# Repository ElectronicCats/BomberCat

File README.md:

# BomberCat

<p align=center>

</p>

<p align=center><b>Where to buy and learn more</b></p>
<p align=center>

</p>

<p align=center>
  
</p>

BomberCat 💣 is the latest security tool that combines the most common card technologies: NFC technology (Near Field Communication) and magnetic stripe technology used in access control, identification, and banking cards.
Specially created to audit banking terminals, and identify NFC readers and sniffing tools, with this tool you can audit, read, or emulate magnetic stripes and NFC cards.

It also has an ESP32 co-processor with WiFiNINA firmware that allows it to make WiFi connections to use with HTTP or MQTT protocols, which will allow relay and spoofing attacks to be tested over long distances or on local web servers.

### Applications
BomberCat features an RP2040 MCU working along with the PN7150 (a recent generation NFC chip). 
The USB interface is provided by the RP2040 MCU and the NFC functionality is guaranteed by the PN7150.

BomberCat is designed to be intuitive for users. Easy to program using frameworks such as Arduino, Circuitpython, and Micropython.  We have prepared a series of examples with which you can start experimenting, check out the examples folder.

**Card emulation mode:** in which BomberCat behaves as a smart card or a tag. In this mode, BomberCat emulates an NFC tag. It does not initiate communication, it only responds to the NFC reader. 
A typical application of the card emulation mode is how people use NFC on their smartphones to replace several cards, badges, or tags at once (using the same smartphone for RFID access controls, contactless payments, etc). 
However, card emulation mode is not only beneficial for smartphones but any type of portable device.

**Read/Write:** in which BomberCat behaves as an NFC reader/writer. In this mode, BomberCat communicates with a passive tag, an NFC smart card, or an NFC device operating in the card emulation mode. It can read or write to a tag (although reading is a more common use case because tags will often be write-protected). In this mode, BomberCat generates an RF field, while a tag or card only modulates it.

**Magspoof:** for magnetic stripes interaction.
Magspoof mode can emulate magnetic stripe cards by emulating the electromagnetic pulses of this type of card.

## NFCGate relay

BomberCat can act as an [NFCGate](https://github.com/nfcgate/nfcgate)-compatible
**relay** endpoint: it pairs with a second NFCGate peer — another BomberCat or the
NFCGate Android app — through an `nfcgate-server`, relaying NFC APDUs over WiFi/TCP.
This makes a card that is physically in one place appear in front of a reader in
another — the classic test for whether a contactless reader accepts a card that is
not really present.

It ships with two pieces, each in its own repository:

- **Relay firmware** — [`bombercat-firmware`](https://github.com/ElectronicCats/bombercat-firmware),
  a role-selectable (`reader` / `card`) sketch built on the `BomberCatCore` library.
- **`bombercat` control CLI** — [`bombercat-tools`](https://github.com/ElectronicCats/bombercat-tools),
  a Python tool that configures, runs, monitors and captures the relay over
  USB-serial (APDU capture opens straight in Wireshark).

> Relay/spoofing features are for **authorized security audits only** — see the
> Disclaimer below.

## Characteristics:
- Cortex M0+ processor
- USB C 2.0
- NFC Reader, Card, and NFC Forum
- Arduino compatible
- 100% CircuitPython compatible
- UF2 Bootloader
- WIFI (WiFiNINA)
- BLE (ArduinoBLE)
- 1 LED status
- Open Hardware
- MagSpoof coil
- Battery
- RF protocols supported
  - NFCIP-1, NFCIP-2 protocol 
  - ISO/IEC 14443A, ISO/IEC 14443B PICC, NFC Forum T4T modes via host interface
  - NFC Forum T3T via host interface
  - ISO/IEC 14443A, ISO/IEC 14443B PCD designed according to NFC Forum digital protocol T4T platform and ISO-DEP 
  - FeliCa PCD mode
  - MIFARE Classic PCD encryption mechanism (MIFARE Classic 1K/4K)
  - NFC Forum tag 1 to 5 (MIFARE Ultralight, Jewel, Open FeliCa tag, MIFAREDESFire
  - ISO/IEC 15693/ICODE VCD mode 
  - Includes NXP ISO/IEC14443-A and Innovatron ISO/IEC14443-B intellectual property licensing rights

## Requirements

- **Arduino IDE:** version 2.3.3
- **Board Package:** Electronic Cats Mbed OS RP2040 Boards version 2.0.0

 Libraries:
 
  - **PubSubClient:** version 2.8.0
  - **WiFiNINA:** version 1.8.14
  - **Electronic Cats PN7150:** version 2.1.0
  - **SerialCommand:** [Arduino-SerialCommand](https://github.com/kroimon/Arduino-SerialCommand) 

### **Linux Setup Instructions**
If you are using Linux, ensure the BomberCat is properly recognized by running the post-install script located at:

`~/.arduino15/packages/electroniccats/hardware/mbed_rp2040/2.0.0/post_install.sh`

This step is essential to ensure the board can be detected and the firmware uploaded successfully.

## Wiki and Getting Started

[Getting Started in our Wiki](https://github.com/ElectronicCats/BomberCat/wiki)

## Repositories

This repository holds the **hardware** design (KiCad, BOM, mechanical files) and
general project documentation. Firmware and host tooling used to live here but were
split out into their own repositories for better version control and issue tracking:

### Firmware Repository
All BomberCat firmware (NFCGate relay, DetectTags, DetectReaders, magspoof, and more)
lives here:

https://github.com/ElectronicCats/bombercat-firmware

All BomberCat versions are supported in this repository — check which version you own
and select the proper branch to develop, build, or program your board.

### Tools Repository
The `bombercat` control CLI and other Python dev tooling live here:

https://github.com/ElectronicCats/bombercat-tools

## Disclaimer
>[!IMPORTANT]
>BomberCat is a wireless penetration testing tool intended **solely for use in authorized security audits, where such usage is permitted by applicable laws and regulations**. Before utilizing this tool, it is crucial to ensure compliance with all relevant legal requirements and obtain appropriate permissions from the relevant authorities.
>
>The board **does not provide** any means or authorization to utilize credit cards or engage in any financial transactions that are not legally authorized. **Electronic Cats holds no responsibility for any unauthorized use of the tool or any resulting damages**.

-------

## How to contribute 
 Contributions are welcome! 

Please read the document  [**Contribution Manual**](https://github.com/ElectronicCats/electroniccats-cla/blob/main/electroniccats-contribution-manual.md)  which will show you how to contribute your changes to the project.

✨ Thanks to all our [contributors](https://github.com/ElectronicCats/BomberCat/graphs/contributors)! ✨

See [**_Electronic Cats CLA_**](https://github.com/ElectronicCats/electroniccats-cla/blob/main/electroniccats-cla.md) for more information.

See the  [**community code of conduct**](https://github.com/ElectronicCats/electroniccats-cla/blob/main/electroniccats-community-code-of-conduct.md) for a vision of the community we want to build and what we expect from it.
 
### Supported by
 Thanks [Wallee](https://en.wallee.com/) for support this open source project

## Maintainer

<p align=center>

</p>

Electronic Cats invests time and resources providing this open-source design, please support Electronic Cats and open-source hardware by purchasing products from Electronic Cats!

### License

Electronic Cats invests time and resources in providing this open-source design, please support Electronic Cats and open-source hardware by purchasing products from Electronic Cats!

Designed by Electronic Cats.

Firmware released under an GNU AGPL v3.0 license. See the LICENSE file for more information.

Hardware released under an CERN Open Hardware Licence v1.2. See the LICENSE_HARDWARE file for more information.

Electronic Cats is a registered trademark, please do not use if you sell these PCBs.

Jul 2022

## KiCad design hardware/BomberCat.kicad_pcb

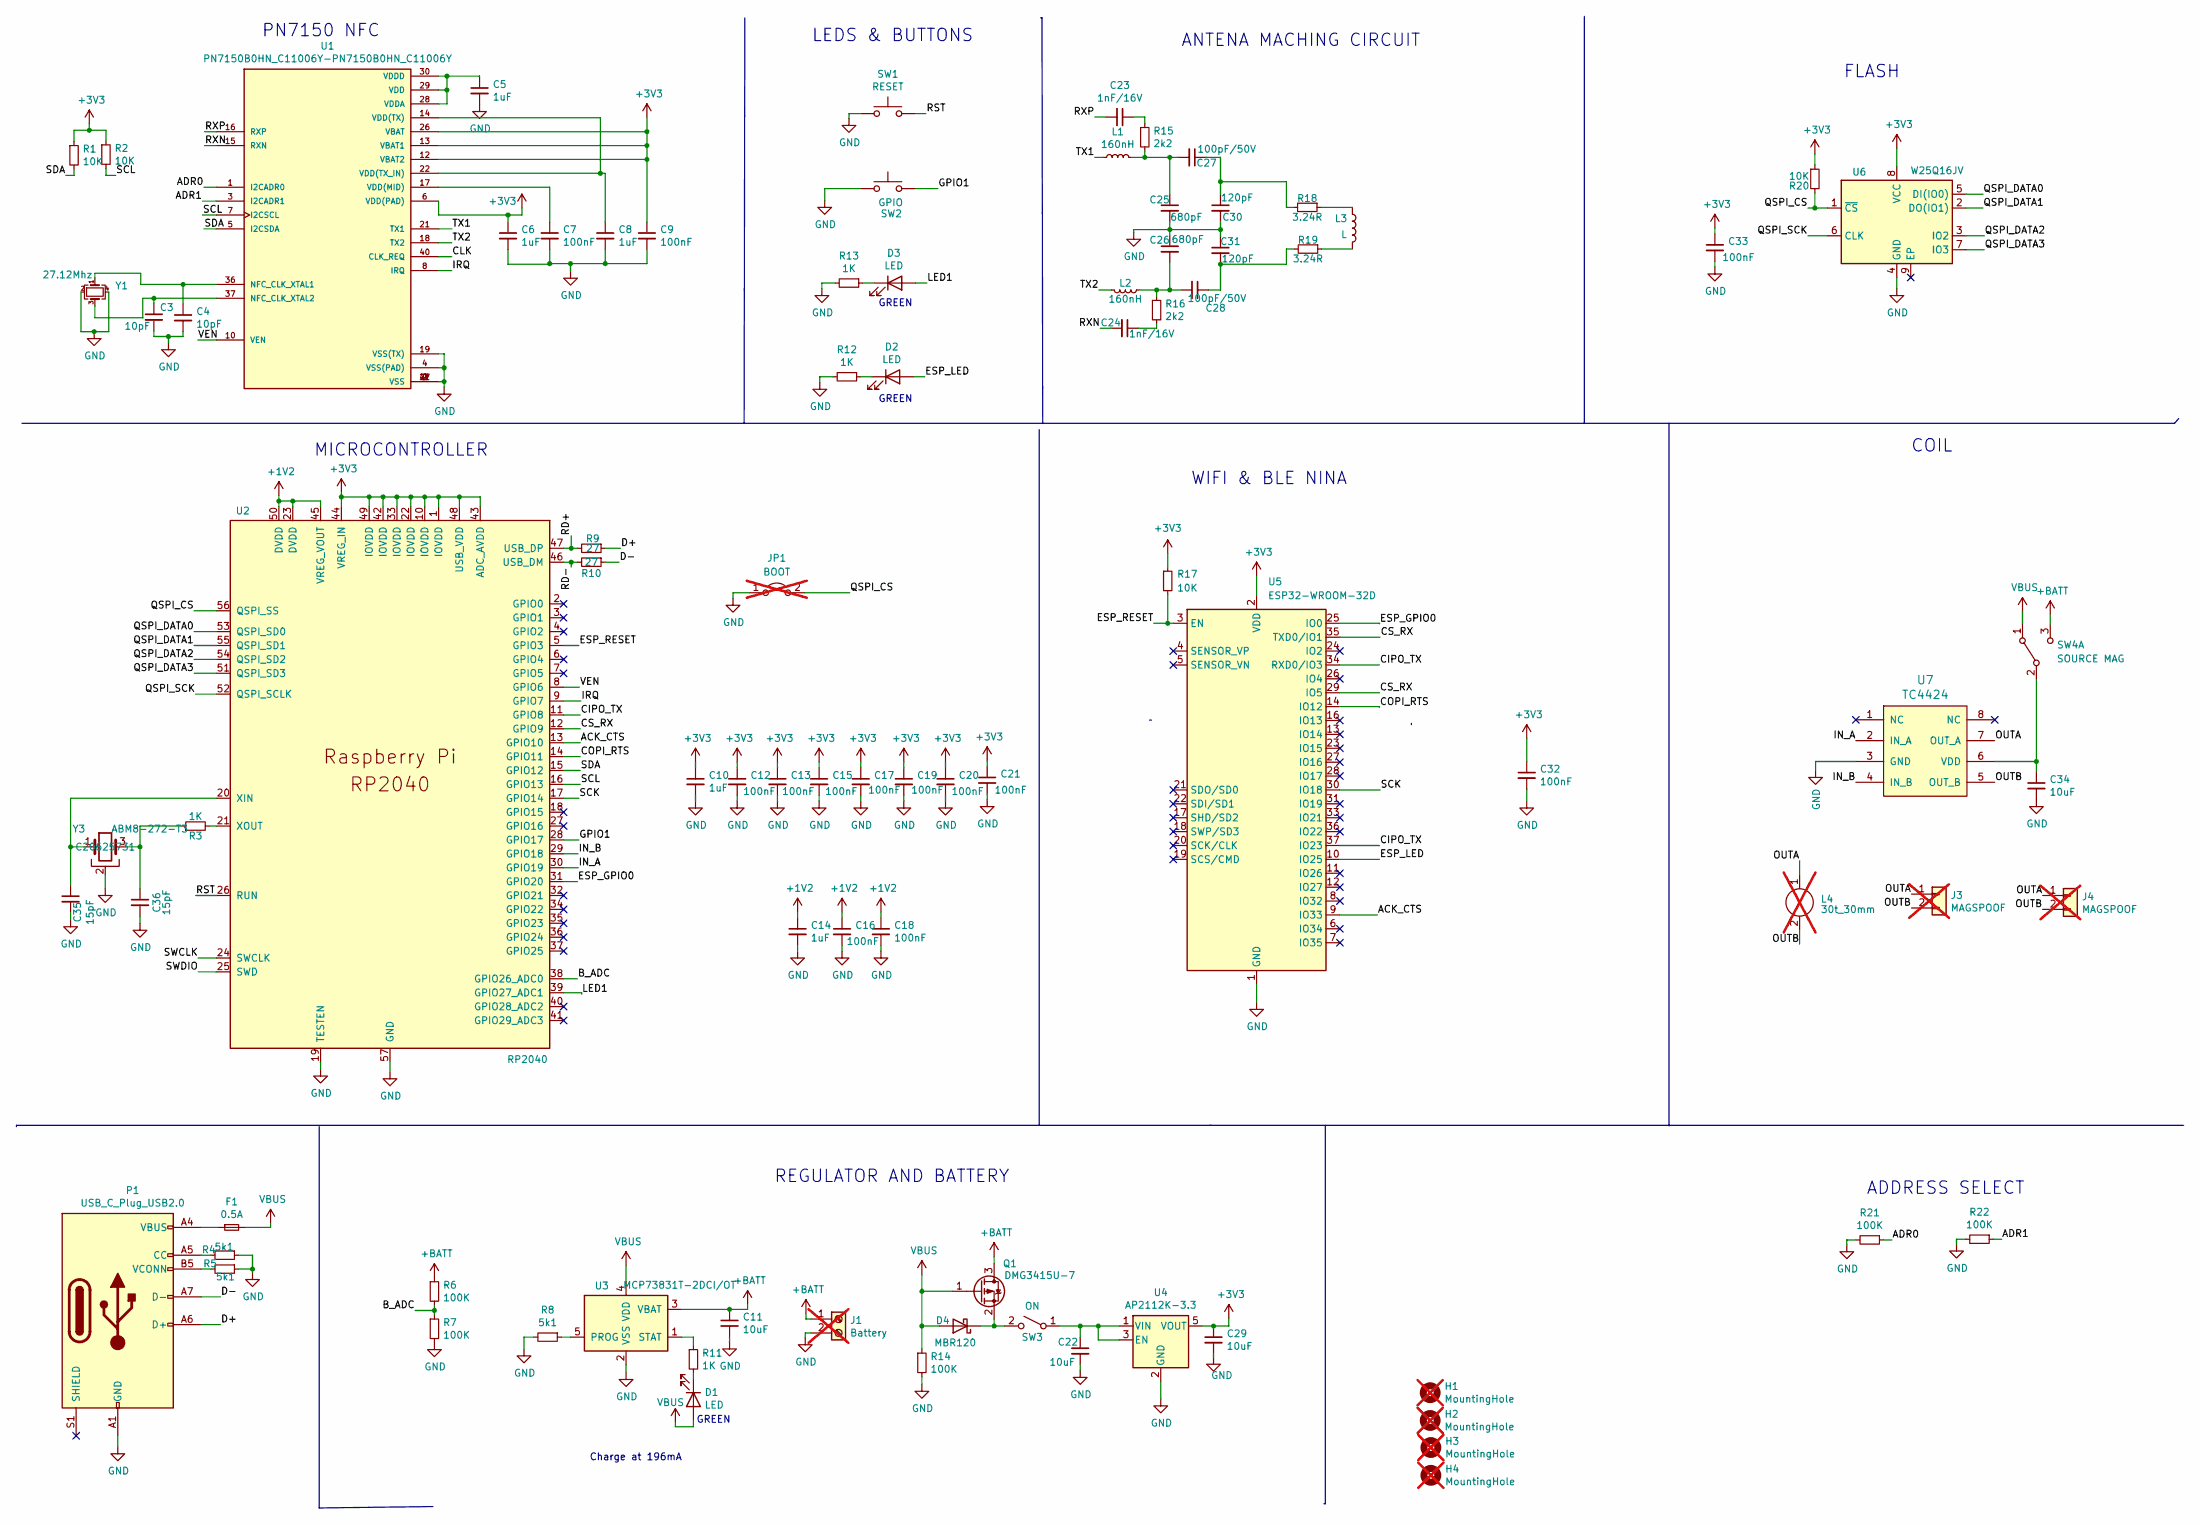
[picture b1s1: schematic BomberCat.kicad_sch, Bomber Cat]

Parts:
C3, C4: 10pF; C_0603_1608Metric; LCSC# C106245
C5, C6, C8: 1uF; C_0603_1608Metric; LCSC# C5673
C7, C9, C12, C13, C15, C16, C17, C18, C19, C20, C21, C32, C33: 100nF; C_0603_1608Metric; LCSC# C282519
C10, C14: 1uF; C_0603_1608Metric; LCSC# C15849
C11, C22: 10uF; C_0603_1608Metric; LCSC# C85713
C23, C24: 1nF/16V; C_0603_1608Metric; LCSC# C519403
C25, C26: 680pF; C_0603_1608Metric; LCSC# C107055
C27, C28: 100pF/50V; C_0603_1608Metric; LCSC# C14665
C29, C34: 10uF; C_0603_1608Metric; LCSC# C96446
C30, C31: 120pF; C_0603_1608Metric; LCSC# C107035
C35, C36: 15pF; C_0603_1608Metric; LCSC# C107037
D1, D2, D3: LED; LED_0805_2012Metric_Pad1.15x1.40mm_HandSolder; LCSC# C965815
D4: MBR120; D_SOD-123F; LCSC# C130880
F1: 0.5A; Fuse_0805_2012Metric; LCSC# C2649565
H1, H2, H3, H4: MountingHole; MountingHole_2.2mm_M2; not fitted
J1: Battery; PinHeader_1x02_P2.54mm_Vertical; not fitted
J3, J4: MAGSPOOF; PinHeader_1x02_P2.54mm_Vertical; not fitted
JP1: BOOT; SolderJumper-2_P1.3mm_Open_TrianglePad1.0x1.5mm; not fitted
L1, L2: 160nH; L_0603_1608Metric_Pad1.05x0.95mm_HandSolder; LCSC# C434822
L3: L; MOLEX_1661; LCSC# C22418213
L4: 30t_30mm; Coil_30t_30mm_0.2_0.2_0.6_0.3; not fitted
P1: USB_C_Plug_USB2.0; C393939; LCSC# C393939
Q1: DMG3415U-7; SOT-23; LCSC# C96616
R1, R2, R17, R20: 10K; R_0603_1608Metric; LCSC# C2930027
R3, R11, R12, R13: 1K; R_0603_1608Metric; LCSC# C112433
R4, R5, R8: 5k1; R_0603_1608Metric; LCSC# C23186
R6, R7, R14, R21, R22: 100K; R_0603_1608Metric; LCSC# C15458
R9, R10: 27; R_0603_1608Metric; LCSC# C403464
R15, R16: 2k2; R_0603_1608Metric; LCSC# C113303
R18, R19: 3.24R; R_0603_1608Metric; LCSC# C166817
SW1: RESET; SW_SPST_TL3342; LCSC# C318884
SW2: GPIO; SW_SPST_TL3342; LCSC# C318884
SW3: ON; JS102011SAQN; LCSC# C221660
SW4: SOURCE MAG; JS202011CQN; LCSC# C221663
U1: PN7150B0HN_C11006Y-PN7150B0HN_C11006Y; QFN-40-1EP_6x6mm_P0.5mm_EP4.6x4.6mm; LCSC# C702907
U2: RP2040; RP2040-QFN-56; LCSC# C2040
U3: MCP73831T-2DCI/OT; SOT-23-5; LCSC# C424093
U4: AP2112K-3.3; SOT-23-5; LCSC# C150742
U5: ESP32-WROOM-32D; ESP32-WROOM-32; LCSC# C473012
U6: W25Q16JV; SON50P200X300X40-9N; LCSC# C2843335
U7: TC4424; SOIC-8_3.9x4.9mm_P1.27mm; LCSC# C7498963
Y1: 27.12Mhz; Crystal_SMD_2016-4Pin_2.0x1.6mm; LCSC# C252276
Y3: ABM8-272-T3; Crystal_SMD_Abracon_ABM8G-4Pin_3.2x2.5mm; LCSC# C20625731

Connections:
+1V2: C14.1, C16.1, C18.1, U2.23 (DVDD), U2.45 (VREG_VOUT), U2.50 (DVDD)
+3V3: C6.1, C9.1, C10.1, C12.1, C13.1, C15.1, C17.1, C19.1, C20.1, C21.1, C29.1, C32.1, C33.1, R1.1, R2.1, R17.1, R20.1, U1.6 (VDD(PAD)), U1.12 (VBAT2), U1.13 (VBAT1), U1.26 (VBAT), U2.1 (IOVDD), U2.10 (IOVDD), U2.22 (IOVDD), U2.33 (IOVDD), U2.42 (IOVDD), U2.43 (ADC_AVDD), U2.44 (VREG_IN), U2.48 (USB_VDD), U2.49 (IOVDD), U4.5 (VOUT), U5.2 (VDD), U6.8 (VCC)
+BATT: C11.1, J1.1, Q1.3 (D), R6.1, SW4.3 (C), U3.3 (VBAT)
/ACK_CTS: U2.13 (GPIO10), U5.9 (IO33)
/ADR0: R21.1, U1.1 (I2CADR0)
/ADR1: R22.1, U1.3 (I2CADR1)
/B_ADC: R6.2, R7.1, U2.38 (GPIO26_ADC0)
/CIPO_TX: U2.11 (GPIO8), U5.34 (RXD0/IO3), U5.37 (IO23)
/CLK: U1.40 (CLK_REQ)
/COPI_RTS: U2.14 (GPIO11), U5.14 (IO12)
/CS_RX: U2.12 (GPIO9), U5.29 (IO5), U5.35 (TXD0/IO1)
/D+: P1.A6 (D+), R9.1
/D-: P1.A7 (D-), R10.1
/ESP_GPIO0: U2.31 (GPIO20), U5.25 (IO0)
/ESP_LED: D2.2 (A), U5.10 (IO25)
/ESP_RESET: R17.2, U2.5 (GPIO3), U5.3 (EN)
/GPIO1: SW2.2, U2.28 (GPIO17)
/IN_A: U2.30 (GPIO19), U7.2 (IN_A)
/IN_B: U2.29 (GPIO18), U7.4 (IN_B)
/IRQ: U1.8 (IRQ), U2.9 (GPIO7)
/LED1: D3.2 (A), U2.39 (GPIO27_ADC1)
/OUTA: J3.1, J4.1, L4.1, U7.7 (OUT_A)
/OUTB: J3.2, J4.2, L4.2, U7.5 (OUT_B)
/QSPI_CS: JP1.2 (B), R20.2, U2.56 (QSPI_SS), U6.1 (~CS)
/QSPI_DATA0: U2.53 (QSPI_SD0), U6.5 (DI(IO0))
/QSPI_DATA1: U2.55 (QSPI_SD1), U6.2 (DO(IO1))
/QSPI_DATA2: U2.54 (QSPI_SD2), U6.3 (IO2)
/QSPI_DATA3: U2.51 (QSPI_SD3), U6.7 (IO3)
/QSPI_SCK: U2.52 (QSPI_SCLK), U6.6 (CLK)
/RD+: R9.2, U2.47 (USB_DP)
/RD-: R10.2, U2.46 (USB_DM)
/RST: SW1.2, U2.26 (RUN)
/RXN: C24.2, U1.15 (RXN)
/RXP: C23.2, U1.16 (RXP)
/SCK: U2.17 (GPIO14), U5.30 (IO18)
/SCL: R2.2, U1.7 (I2CSCL), U2.16 (GPIO13)
/SDA: R1.2, U1.5 (I2CSDA), U2.15 (GPIO12)
/SWCLK: U2.24 (SWCLK)
/SWDIO: U2.25 (SWD)
/TX1: L1.1, U1.21 (TX1)
/TX2: L2.2, U1.18 (TX2)
/VEN: U1.10 (VEN), U2.8 (GPIO6)
GND: C3.2, C4.2, C5.2, C6.2, C7.2, C8.2, C9.2, C10.2, C11.2, C12.2, C13.2, C14.2, C15.2, C16.2, C17.2, C18.2, C19.2, C20.2, C21.2, C22.2, C25.2, C26.1, C29.2, C30.2, C31.1, C32.2, C33.2, C34.2, C35.2, C36.2, J1.2, JP1.1 (A), P1.A1 (GND), P1.A12 (GND), P1.B1 (GND), P1.B12 (GND), R4.1, R5.1, R7.2, R8.2, R12.2, R13.2, R14.2, R21.2, R22.2, SW1.1, SW2.1, U1.2 (VSS), U1.4 (VSS(PAD)), U1.9 (VSS), U1.19 (VSS(TX)), U1.27 (VSS), U1.41 (VSS), U2.19 (TESTEN), U2.57 (GND), U3.2 (VSS), U4.2 (GND), U5.1 (GND), U5.15 (GND), U5.38 (GND), U5.39 (GND), U6.4 (GND), U7.3 (GND), Y1.2, Y1.4, Y3.2
unnamed: C23.1, R15.1
unnamed: C24.1, R16.2
unnamed: C25.1, C27.2, L1.2, R15.2
unnamed: C26.2, C28.2, L2.1, R16.1
unnamed: C27.1, C30.1, R18.2
unnamed: C28.1, C31.2, R19.2
unnamed: C36.1, R3.1, Y3.3
unnamed: D1.1 (K), R11.2
unnamed: D2.1 (K), R12.1
unnamed: D3.1 (K), R13.1
unnamed: D4.1 (K), Q1.2 (S), SW3.2 (B)
unnamed: F1.1, P1.A4 (VBUS), P1.A9 (VBUS), P1.B4 (VBUS), P1.B9 (VBUS)
unnamed: L3.1, R18.1
unnamed: L3.2, R19.1
unnamed: P1.A5 (CC), R4.2
unnamed: P1.B5 (VCONN), R5.2
unnamed: C22.1, SW3.1 (A), U4.1 (VIN), U4.3 (EN)
unnamed: C34.1, SW4.2 (B), U7.6 (VDD)
unnamed: C4.1, U1.36 (NFC_CLK_XTAL1), Y1.1
unnamed: C3.1, U1.37 (NFC_CLK_XTAL2), Y1.3
unnamed: C7.1, U1.17 (VDD(MID))
unnamed: C8.1, U1.14 (VDD(TX)), U1.22 (VDD(TX_IN))
unnamed: C5.1, U1.28 (VDDA), U1.29 (VDD), U1.30 (VDDD)
unnamed: C35.1, U2.20 (XIN), Y3.1
unnamed: R3.2, U2.21 (XOUT)
unnamed: R8.1, U3.5 (PROG)
unnamed: R11.1, U3.1 (STAT)
VBUS: D1.2 (A), D4.2 (A), F1.2, Q1.1 (G), R14.1, SW4.1 (A), U3.4 (VDD)

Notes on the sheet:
GREEN
COIL
Charge at 196mA
ANTENA MACHING CIRCUIT
PN7150 NFC
LEDS & BUTTONS
WIFI & BLE NINA
MICROCONTROLLER
REGULATOR AND BATTERY
FLASH
ADDRESS SELECT

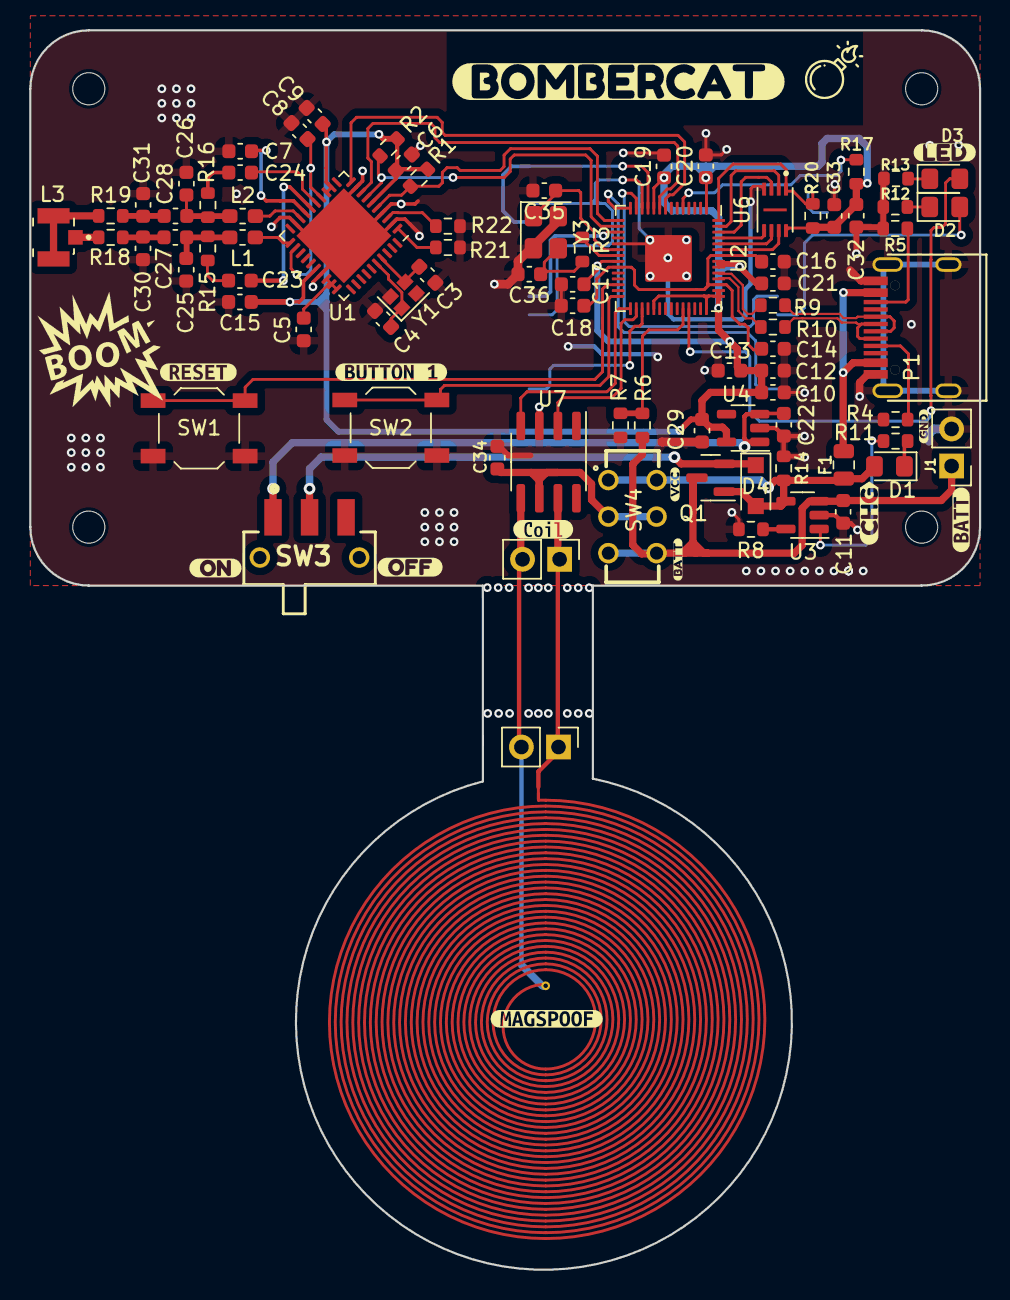
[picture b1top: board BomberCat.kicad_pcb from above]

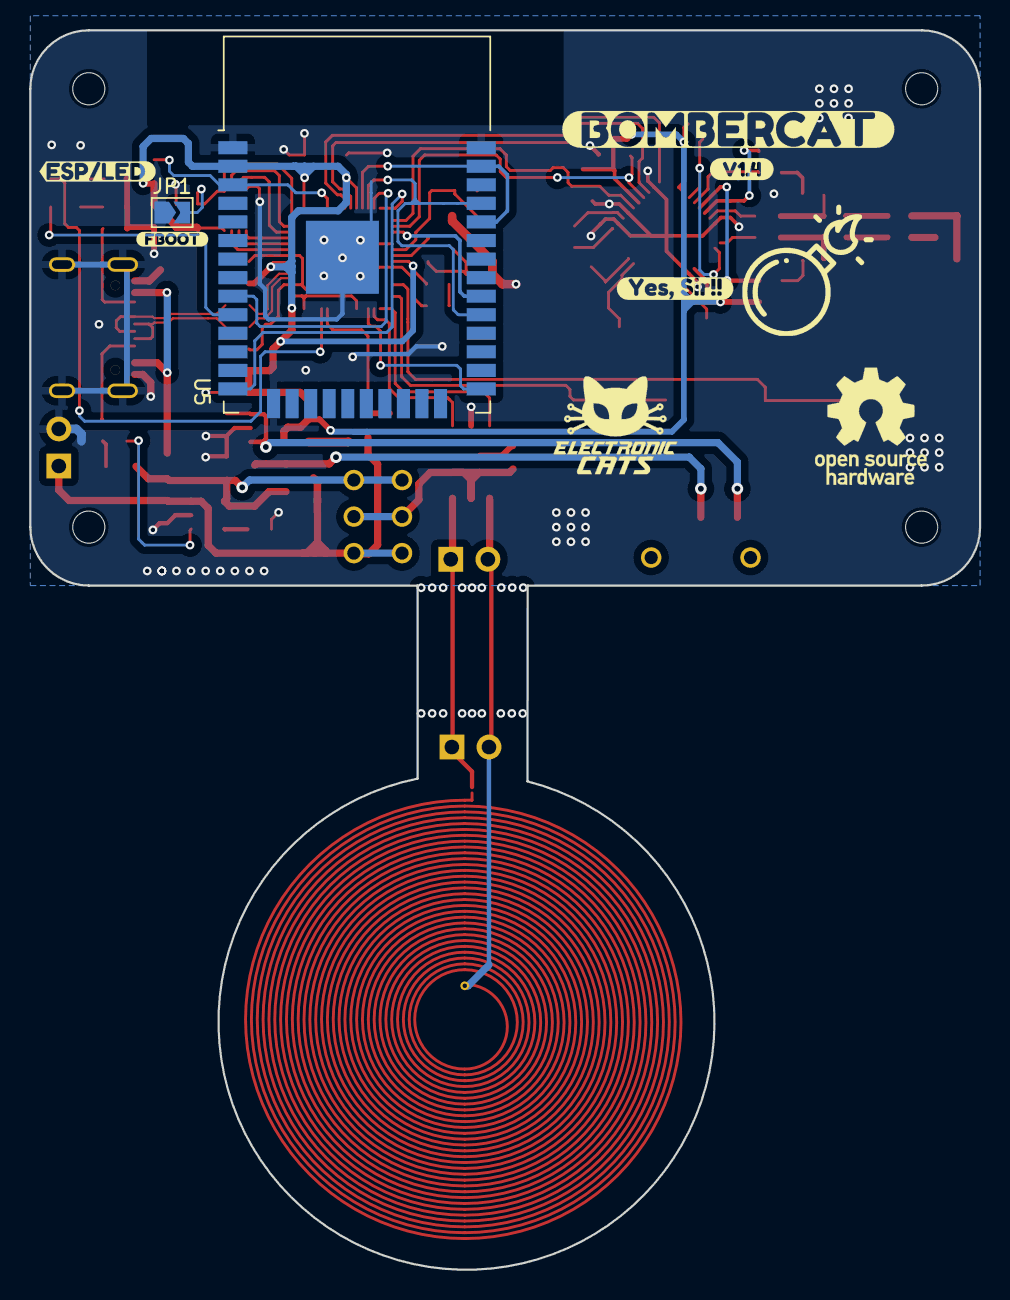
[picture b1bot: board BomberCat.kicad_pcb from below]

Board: 2 copper layers, 65.0 x 84.8 mm, 106 parts (7 on the bottom side), 68 nets.

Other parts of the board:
kibuzzard-62CC5B78, kibuzzard-62CC5B78#2: G***; kibuzzard-62CC5B78
kibuzzard-62CC5BEF: G***; kibuzzard-62CC5BEF
kibuzzard-62CC9A49: G***; kibuzzard-62CC9A49
kibuzzard-62CC595D: G***; kibuzzard-62CC595D
kibuzzard-62CC5892: G***; kibuzzard-62CC5892
kibuzzard-62E1B288: G***; kibuzzard-62E1B288
kibuzzard-62E1B296: G***; kibuzzard-62E1B296
kibuzzard-62E41048: G***; kibuzzard-62E41048
kibuzzard-67E317B3: G***; kibuzzard-67E317B3
kibuzzard-67F6D9A7: G***; kibuzzard-67F6D9A7
kibuzzard-67F6D96D: G***; kibuzzard-67F6D96D
kibuzzard-67F6D992: G***; kibuzzard-67F6D992
kibuzzard-67F6E5D9: G***; kibuzzard-67F6E5D9
kibuzzard-67F6E601: G***; kibuzzard-67F6E601
kibuzzard-67FD52FB: G***; kibuzzard-67FD52FB
kibuzzard-67FEA7C0: G***; kibuzzard-67FEA7C0
kibuzzard-698D0712: G***; kibuzzard-698D0712

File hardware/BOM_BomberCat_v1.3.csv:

"Value","Reference","Footprint","LCSC#","Qty","DNP","manf#"
"ABM8-272-T3","Y3","Crystal:Crystal_SMD_Abracon_ABM8G-4Pin_3.2x2.5mm","C20625731 ","1","",""
"27.12Mhz","Y1","Crystal:Crystal_SMD_2016-4Pin_2.0x1.6mm","C252276","1","","520-271.2-6-37-JTNT"
"TC4424","U7","Package_SO:SOIC-8_3.9x4.9mm_P1.27mm","C7498963 ","1","","TC4424AVOA"
"W25Q16JV","U6","BomberCat:SON50P200X300X40-9N","C2843335","1","","W25Q16JVUUIQ"
"ESP32-WROOM-32D","U5","RF_Module:ESP32-WROOM-32","C473012","1","","ESP32M4"
"AP2112K-3.3","U4","Package_TO_SOT_SMD:SOT-23-5","C150742","1","","AP7365-33WG-7"
"MCP73831T-2DCI/OT","U3","Package_TO_SOT_SMD:SOT-23-5","C424093","1","","MCP73831T-2DCI/OT "
"RP2040","U2","BomberCat:RP2040-QFN-56","C2040","1","","RP2040"
"PN7150B0HN_C11006Y-PN7150B0HN_C11006Y","U1","Package_DFN_QFN:QFN-40-1EP_6x6mm_P0.5mm_EP4.6x4.6mm","C702907","1","","PN7150B0HN/C11002Y"
"SOURCE MAG","SW4","BomberCat:JS202011CQN","C221663","1","","JS202011CQN"
"ON","SW3","BomberCat:JS102011SAQN","C221660","1","","JS102011SAQN"
"GPIO","SW2","Button_Switch_SMD:SW_SPST_TL3342","C318884","1","",""
"RESET","SW1","Button_Switch_SMD:SW_SPST_TL3342","C318884","1","",""
"3.24R","R18,R19","Resistor_SMD:R_0603_1608Metric","C166817","2","","RC0603FR-073R4"
"2k2","R15,R16","Resistor_SMD:R_0603_1608Metric","C113303","2","","RC0603JR-072K2L"
"27","R9,R10","Resistor_SMD:R_0603_1608Metric","C403464","2","","ERJ3GEYJ270V"
"100K","R6,R7,R14,R21,R22","Resistor_SMD:R_0603_1608Metric","C15458","5","",""
"5k1","R4,R5,R8","Resistor_SMD:R_0603_1608Metric","C23186","3","",""
"1K","R3,R11,R12,R13","Resistor_SMD:R_0603_1608Metric","C112433","4","","WR06X1001FTL"
"10K","R1,R2,R17,R20","Resistor_SMD:R_0603_1608Metric","C2930027","4","",""
"DMG3415U-7","Q1","Package_TO_SOT_SMD:SOT-23","C96616","1","","DMG3415U-7"
"USB_C_Plug_USB2.0","P1","Connectors:C393939","C393939","1","",""
"30t_30mm","L4","BomberCat:Coil_30t_30mm_0.2_0.2_0.6_0.3","","1","DNP",""
"L","L3","Connectors:MOLEX_1661","C22418213","1","","CONUFL001-SMD-T "
"160nH","L1,L2","Inductor_SMD:L_0603_1608Metric_Pad1.05x0.95mm_HandSolder","C434822","2","","MLJ1608WR16JT000"
"MAGSPOOF","J3,J4","Connector_PinHeader_2.54mm:PinHeader_1x02_P2.54mm_Vertical","","2","DNP",""
"Battery","J1","Connector_PinHeader_2.54mm:PinHeader_1x02_P2.54mm_Vertical","-","1","DNP","-"
"MountingHole","H1,H2,H3,H4","MountingHole:MountingHole_2.2mm_M2","-","4","DNP","-"
"0.5A","F1","Fuse:Fuse_0805_2012Metric","C2649565","1","","MFU0805FF00500P100"
"MBR120","D4","Diode_SMD:D_SOD-123F","C130880","1","","MBR120LSF"
"LED","D1,D2,D3","LED_SMD:LED_0805_2012Metric_Pad1.15x1.40mm_HandSolder","C965815","3","","XL-2012UGC"
"15pF","C35,C36","Capacitor_SMD:C_0603_1608Metric","C107037","2","",""
"120pF","C30,C31","Capacitor_SMD:C_0603_1608Metric","C107035","2","","CC0603JRNPO9BN121"
"10uF","C29,C34","Capacitor_SMD:C_0603_1608Metric","C96446","2","","CL10A106MA8NRNC"
"100pF/50V","C27,C28","Capacitor_SMD:C_0603_1608Metric","C14665","2","","06035A101JAT4A"
"680pF","C25,C26","Capacitor_SMD:C_0603_1608Metric","C107055","2","","885012206107"
"1nF/16V","C23,C24","Capacitor_SMD:C_0603_1608Metric","C519403","2","",""
"10uF","C11,C22","Capacitor_SMD:C_0603_1608Metric","C85713","2","",""
"1uF","C10,C14","Capacitor_SMD:C_0603_1608Metric","C15849","2","",""
"100nF","C7,C9,C12,C13,C15,C16,C17,C18,C19,C20,C21,C32,C33","Capacitor_SMD:C_0603_1608Metric","C282519","13","",""
"1uF","C5,C6,C8","Capacitor_SMD:C_0603_1608Metric","C5673","3","",""
"10pF","C3,C4","Capacitor_SMD:C_0603_1608Metric","C106245","2","","CC0603JRNPO9BN100"

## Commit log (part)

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2022-10-18 cordinator for link client/host
2022-10-18 code not required is removed
2022-10-19 more time send init magspoof
2022-10-19 clean code host
2022-10-19 clean more code
2022-10-19 fixed wifi Store value
2022-10-19 fixed wifi Store value client
2022-10-19 new struc for reconnect wifi and mqtt
2022-10-19 host released at startup and when magstrip is read
2022-10-20 fix host and client topic
2022-10-21 wait conecct from host first data
2022-10-21 HMAX hosts/clients
2022-11-15 added case stl files
2022-11-16 remove detect Mifare
2022-11-17 New client added and status update
2022-11-17 notification no detect card and reset host status
2022-11-17 update status when new client
2022-11-23 OK replies
2022-11-25 Added new top logo
2022-11-28 Automated command test script (client)
2022-11-28 fix square bracket
2022-11-30 test BomberCat script, client no respond while host is selected
2022-12-06 host selected in loop, optional update in cordinator
2022-12-07 Remove debug prints, update test_script
2022-12-08 change flags and led error, remove ERROR prints
2022-12-13 Added reconnect flag, resolves setup_mqtt bug
2022-12-14 MQTT server can be set in command line
2022-12-19 fix split tracks
2022-12-23 remove print
2022-12-23 fix magspoof csv
2022-12-24 Update examples magspoof
2023-01-06 add BOM connector antenna
2023-01-11 WifiServerTest compilation OK
    The file compiles correctly, trying to convert the html file to String or another type so Arduino will be able to open it.
2023-01-12 reduces the number of connection attempts
2023-01-13 add set_n to commands
    for setting number of client/host
2023-01-25 Optimzed code
2023-01-25 DetectTags added to the code
2023-01-31 add test_card command
2023-02-01 Added comments
2023-02-01 Show detected Cards in html
2023-02-10 delay dependent of CmdSize in visamsd
2023-02-13 added set_delay (for testing)
2023-02-16 fix set_delay, comments in test script
2023-02-20 set_delay value stored in flash
2023-04-11 refactor: create a runServer function
2023-04-11 feat: add an index.html.h with a single title
2023-04-11 update to kicad7
2023-04-12 refactor: move the css to its own file
2023-04-13 feat: add the default styles for the login page
2023-04-13 test: alert using javascript
2023-04-13 test: get an overflow when the html is too big
2023-04-13 test: use multiple lines of javascript code without styles
2023-04-13 test: avoid the memory overflow with a buffer
2023-04-13 test: improve speed by increasing the buffer size
2023-04-13 feat: load the css with a buffer
2023-04-13 docs: add comments to the showWebPage function
2023-04-13 refactor: make showPageContent generic
2023-04-14 feat: add a script to convert css files into header files
2023-04-14 feat: convert html, css and js files into header files
2023-04-14 feat: add the rest of the styles
2023-04-14 refactor: delete the replace double quotes or backslashes in the content
2023-04-14 feat: add the logo to the login screen
2023-04-14 feat: add a padding to the logo title and make the logo green
2023-04-14 refactor: change the spaces before the input placeholder by a padding
2023-04-18 docs: add the name of the logo in a comment
2023-04-18 feat: move from one page to another
2023-04-18 fix: center the logo and the logo title
2023-04-18 feat: add the ec logo to the home page
2023-04-19 feat: add the nfc, wifi, github and magspoof icons to the home page
2023-04-19 refactor: change the color of the icons from black to a light gray
2023-04-19 feat: add the info logo to the home page
2023-04-19 feat: add the log out icon to the home page
2023-04-19 feat: add an option to return to the login page
2023-04-20 feat: add the info page
2023-04-20 refactor: url definitions
2023-04-21 fix: change the color of the footer icon link according to the current page
2023-04-21 fix: center the footer icon links
2023-04-21 feat: add a main section
2023-04-21 fix: remove the top margin of the main section
2023-04-21 feat: the github examples link opens a new window
2023-04-26 refactor: rename project name
2023-04-26 feat: set a static ip address
2023-04-26 refactor: rename main.html to login.html
2023-04-27 feat: add an alert to the config device button
2023-04-27 feat: add the magspoof page
2023-04-27 feat: add the card icon
2023-05-02 refactor: add track text fields
2023-05-03 fix: green color con login screen
2023-05-03 fix: info page do not return to login screen
2023-05-03 fix: set to left the card icon
2023-05-03 update 12Mhz cristal part number
2023-05-03 fix: center info content
2023-05-06 feat: get the tracks from the server
2023-05-06 feat: set the button pressed on the query request
2023-05-10 feat: add scripts to compile and upload using arduino-cli
2023-05-10 feat: add magspoof
2023-05-10 refactor: format the code using google's styles guide
2023-05-10 fix: run magspoof without blocking the main thread
2023-05-11 feat: run magspoof with the emulate button
2023-05-11 feat: add user tracks to magspoof
2023-05-11 fix: set github examples link to the bombercat repository
2023-05-16 refactor: change the title from nfc copy cat to bombercat
2023-05-17 feat: add the nfc configurations page
2023-05-18 docs: add a design docs draft
2023-05-18 feat: update the content of the info page
2023-05-30 feat: add a makefile
2023-05-30 test: hardcoded tracks
2023-05-31 feat: add magspoof example
2023-05-31 feat: run the magspoof example
2023-06-03 test: change tracks size
2023-06-05 test: check void char
2023-06-05 test: move string tracks into tracks array
2023-06-05 refactor: add load page content function
2023-06-05 fix: replace plus symbols with spaces
2023-06-06 feat: add format code
2023-06-06 feat: disable save button
2023-06-06 feat: save tracks in local storage
2023-06-06 fix: do not validate empty tracks
2023-06-06 feat: print password
2023-06-06 refactor: remove the connection of a network code
2023-06-07 fix: remove format code
2023-06-07 feat: remove WiFiWebServerTest
2023-06-07 feat: remove magspoof example
2023-06-07 test: harcoded tracks
2023-06-07 docs: update readme - add libraries required - add platform required - remove arduino_secrets - add connection to wifi station
2023-06-08 feat: add the detect tags example
2023-06-08 fix: run detect tags without blocking the main thread
2023-06-09 test: send content to the client
2023-06-09 fix: memory overflow by strcpy
2023-06-09 feat: show poll mode on the server page
2023-06-12 fix: center nfc and magspoof content
2023-06-12 fix: center main content vertically only on desktop mode
2023-06-12 feat: show nfc data
2023-06-12 feat: run detect tags with the read button
2023-06-13 refactr: reload the page with javascript
2023-06-13 feat: add a remove card alert
2023-06-13 feat: show an error alert when reading an nfc tag fails
2023-06-13 add LICENSE hardware
2023-06-13 Create LICENSE
2023-06-14 feat: add the bit rate, afi and dsfid parameters
2023-06-14 fix: do not show failed read alert the first time
2023-06-14 feat: add a clear button
2023-06-16 Add disclaimer
2023-06-16 feat: emulate an nfc tag
2023-06-17 feat: add emulate nfc id function
2023-06-17 test: counter to exit emulate nfc tag function
2023-06-19 refactor: replace apdus with dummy data
2023-06-20 feat: set a timeout to finish emulating nfc id
2023-06-21 feat: emulate nfc id with the button
2023-06-21 feat: add stop loader
2023-06-22 fix: emulate function not working
2023-06-22 test: elapsed time in run server
2023-06-23 feat: toggle emulate and stop button state
2023-06-23 feat: change the stop button appearance
2023-06-23 fix: set emulate button as default
2023-06-23 refactor: remove huntercat code
2023-06-23 refactor: run server methods
2023-06-26 feat: remove arduino secrets
2023-06-26 fix: reduce loading time after pressing emulate nfc id
2023-06-26 fix: reduce loading time by reducing the number of read attempts from 5 to 2
2023-06-26 fix: stop emulate animation after pressing clear or read
2023-06-27 feat: add preferences library
2023-06-27 docs(readme): add preferences library
2023-06-27 feat: add ssid and pass to preferences
2023-06-28 feat: add config page
2023-06-28 feat: show current ssid and password in the user interface
2023-06-28 fix: prevent clearing nfc values during web request update
2023-06-28 test: config parameters
2023-06-29 feat: add a factory reset function
2023-06-29 feat: add username and password fields
2023-06-29 test: get wifi ssid
2023-06-29 feat: add user preferences for password change feature
2023-06-30 feat: add user preferences for ssid change feature
2023-06-30 refactor: add trim to decode url function
2023-06-30 feat: reset bombercat after getting new ssid and password
2023-06-30 feat: show alert to reboot the bombercat
2023-07-01 feat: validate password length
2023-07-01 feat: validate ssid length
2023-07-03 feat: add factory reset
2023-07-04 fix: restore magspoof
2023-07-04 feat: remove config device section
2023-07-04 refactor: replace log out icon with store icon
2023-07-04 feat: add back button
2023-07-04 feat: switch debug mode from ui
2023-07-04 feat: add factory reset listener
2023-07-05 docs(readme): add user guide
2023-07-05 docs(readme): add common issues
2023-07-10 test: tracks with spaces
2023-07-19 refactor: restore default tracks
2023-07-19 feat: add navigation buttons on menu bar
2023-07-19 feat: show menu bar only on desktop mode
2023-07-19 feat: set max width for main content
2023-07-19 fix: save sel res on no mifare classic cards
2023-08-02 feat: use variable tracks instead of constant tracks
2023-08-02 fix: decode track 1
2023-08-02 refactor: remove unnecessary code comments
2023-12-18 Update README
    Add the wiki button.
2023-12-22 change store button
2024-01-09 Add_Step_File
2024-04-09 docs: update README.md
    to add contribution notes.
2024-04-26 feat(docs): Add distributor button and text
2024-04-30 fix(docs): correct directory name
2024-04-30 fix(docs): fix readme typo
2024-06-26 fix: ID keep value after wrong wifi
2024-06-26 chore: remove comments
2024-09-02 feat: PN7150 1.8.0 library compatible
2024-09-13 refactor: update host to PN7150 library functions
2024-09-13 refactor: update host functions PN7150 library 2.1.0
2024-09-17 refactor: host working fine
2024-09-23 feat: host mode 1,2 set using new functions
2024-09-23 chore: ignore .bin
2024-09-25 refactor: host-client working
2024-09-25 refactor: client using last functions lib PN7150
2024-10-03 Addition Maintainer button.md
2024-10-03 Maintainer button added
2024-10-18 chore: update README.md
2024-10-18 chore: unnecessary comments were removed
2024-10-18 chore: debug disabled
2024-11-06 feat: change path scripts python and lua
2024-12-04 feat: Code for the Downgrade example was added
2024-12-04 feat: V1.5 of the MagSpoofMQTT example was added.
2024-12-06 feat: Depuration added.
    Code was added to help in the depuration of the sent of the APDU commands to the NFC card. Now it prints it in the Serial monitor
2025-01-16 feat(firmware): to ignore mismatching messages
    Any message without the sentinels (%, ?, or ;) will be ignored and the user will be notified via Serial Monitor.
2025-02-26 fix: nfcread function
2025-03-07 feat(hw): update components labels
2025-03-14 feat(fw): update PN7150 API
2025-03-18 feat: add second version of Downgrade example
2025-03-21 feat: add extract data function
2025-03-24 feat(hw): add Embedded Antenna
2025-03-25 feat(hw): update Antenna
2025-03-25 fix(hw): update Thickness specifications
2025-04-07 fix (hw): Update part numbers
2025-04-07 fix(hw): Update Batt Label
2025-04-08 fix(hw): Update LCSC part numbers in schematic
    Updates the LCSC part numbers in the schematic to ensure their availability
2025-04-09 fix(hw): update BOM
2025-04-14 feat(hw): update routes and resize coil arm
2025-04-15 fix(hw):update labels
2025-04-15 feat(hw): update tracks, remove switch position change and resize coil arm,
2025-04-15 fix(hw): update tracks width
2025-04-15 fix(hw): update manf#s
2025-05-07 fix(hw): update PN7150 module version
2025-06-12 feat(hw): update Y3 footprint
2025-06-13 feat(Hw):Update_BoM
2025-06-13 fix(Hw):PN7150_Updated
2025-07-15 update: examples use PN7150 v3.1.0
    DetectTags and WifiWebServer updated
2025-07-15 update: examples use PN7150
    Host Relay and Client Relay
2025-07-16 fix: populate strings with card data
